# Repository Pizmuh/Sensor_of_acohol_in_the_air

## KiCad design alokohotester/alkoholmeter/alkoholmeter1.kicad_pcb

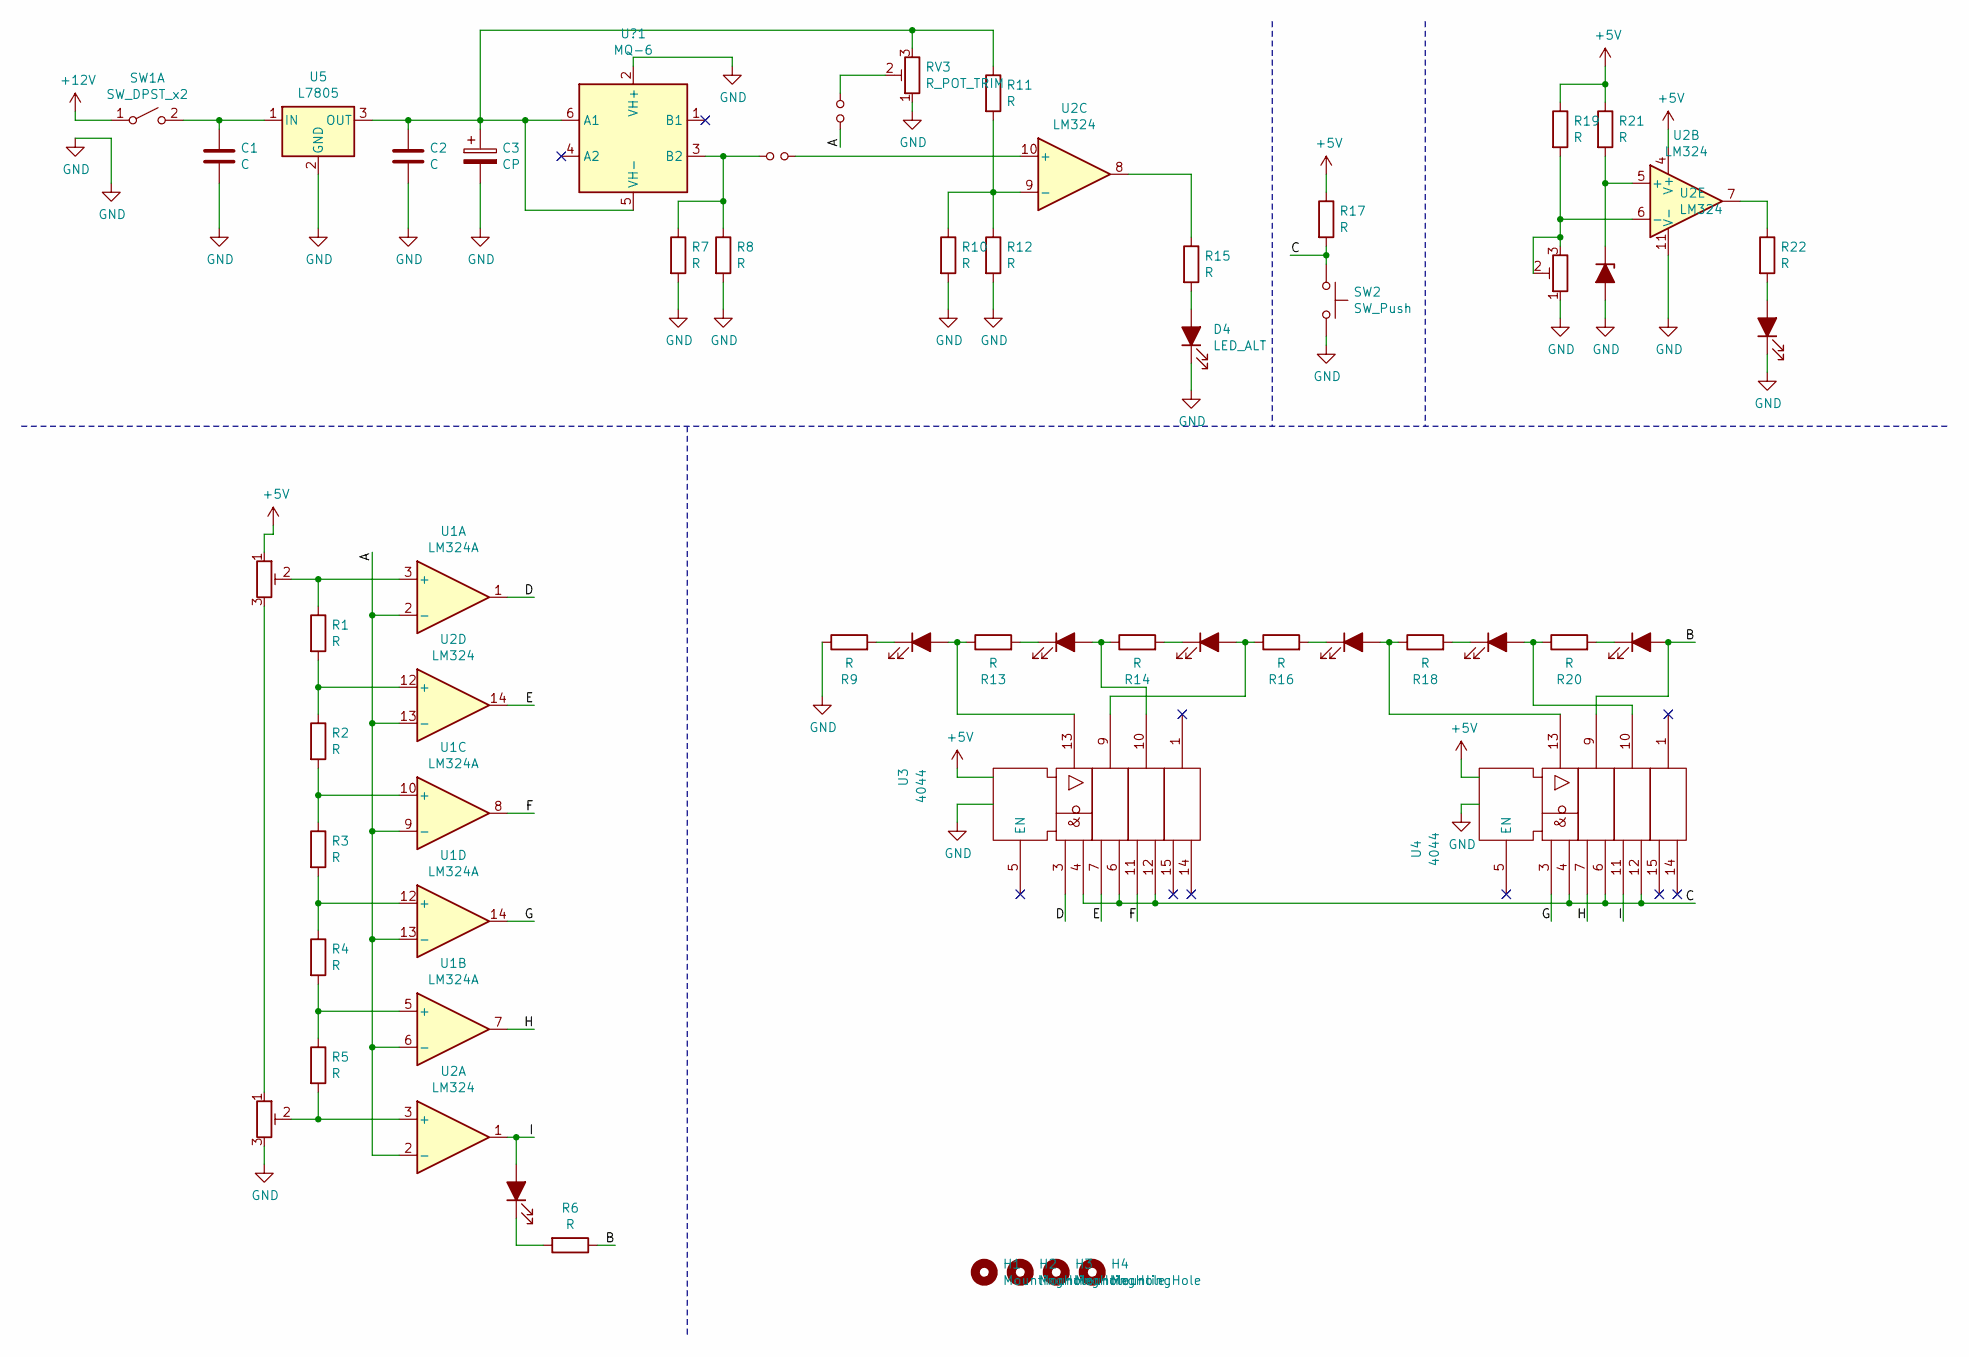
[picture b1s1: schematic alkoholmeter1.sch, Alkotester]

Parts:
C1, C2: C; CP_Radial_D5.0mm_P2.00mm
C3: CP; CP_Radial_D5.0mm_P2.00mm
D1, D2, D3, D4, D5, D6, D7, D9, D10: LED_ALT; LED_D5.0mm
D8: D_Zener_ALT; D_5KPW_P12.70mm_Horizontal
H1, H2, H3, H4: MountingHole; MountingHole_2.5mm
JP1, JP2: Jumper_NO_Small; SolderJumper-2_P1.3mm_Open_Pad1.0x1.5mm
R1, R2, R3, R4, R5, R6, R7, R8, R9, R10, R11, R12, R13, R14, R15, R16, R17, R18, R19, R20, R21, R22: R; R_Axial_DIN0207_L6.3mm_D2.5mm_P7.62mm_Horizontal
RV1, RV2, RV3, RV4: R_POT_TRIM; Potentiometer_ACP_CA6-H2,5_Horizontal
SW1: SW_DPST_x2; SW_E-Switch_EG1224_SPDT_Angled
SW2: SW_Push; SW_PUSH_6mm_H7.3mm
U1: LM324A; DIP825W47P254L1917H533Q14
U2: LM324; DIP825W47P254L1917H533Q14
U3, U4: 4044; DIL16
U5: L7805; TO254P470X1016X2019-3P
U?1: MQ-6

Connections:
+5V: R17.1, R19.1, R21.1, RV1.1, U2.4 (V+), U3.16 (Vdd), U4.16 (Vdd)
+12V: SW1.1 (A)
/A: JP2.1, U1.2 (-), U1.6 (-), U1.9 (-), U1.13 (-), U2.2 (-), U2.13 (-)
/B: D9.2 (A), R6.1, U4.9
/C: R17.2, SW2.1, U3.4, U3.6, U3.12, U4.4, U4.6, U4.12
/D: U1.1, U3.3
/E: U2.14, U3.7
/F: U1.8, U3.11
/G: U1.14, U4.3
/H: U1.7, U4.7
/I: D1.2 (A), U2.1, U4.11
GND: C1.2, C2.2, C3.2, D4.1 (K), D8.2 (A), D10.1 (K), R7.2, R8.2, R9.1, R10.2, R12.2, RV2.3, RV3.1, RV4.1, SW2.2, U2.11 (V-), U3.8 (Vss), U4.8 (Vss), U5.2 (GND), U?1.2 (VH+)
unnamed: C1.1, SW1.2 (B), U5.1 (IN)
unnamed: C2.1, C3.1, R11.1, RV3.3, U5.3 (OUT), U?1.5 (VH-), U?1.6 (A1)
unnamed: D1.1 (K), R6.2
unnamed: D2.1 (K), R9.2
unnamed: D2.2 (A), R13.1, U3.13
unnamed: D3.1 (K), R13.2
unnamed: D3.2 (A), R14.1, U3.10
unnamed: D4.2 (A), R15.2
unnamed: D5.1 (K), R14.2
unnamed: D5.2 (A), R16.1, U3.9
unnamed: D6.1 (K), R16.2
unnamed: D6.2 (A), R18.1, U4.13
unnamed: D7.1 (K), R18.2
unnamed: D7.2 (A), R20.1, U4.10
unnamed: D8.1 (K), R21.2, U2.5 (+)
unnamed: D9.1 (K), R20.2
unnamed: D10.2 (A), R22.2
unnamed: JP1.1, R7.1, R8.1, U?1.3 (B2)
unnamed: JP1.2, U2.10 (+)
unnamed: JP2.2, RV3.2
unnamed: R1.1, RV1.2, U1.3 (+)
unnamed: R1.2, R2.1, U2.12 (+)
unnamed: R2.2, R3.1, U1.10 (+)
unnamed: R3.2, R4.1, U1.12 (+)
unnamed: R4.2, R5.1, U1.5 (+)
unnamed: R5.2, RV2.2, U2.3 (+)
unnamed: R10.1, R11.2, R12.1, U2.9 (-)
unnamed: R15.1, U2.8
unnamed: R19.2, RV4.2, RV4.3, U2.6 (-)
unnamed: R22.1, U2.7
unnamed: RV1.3, RV2.1

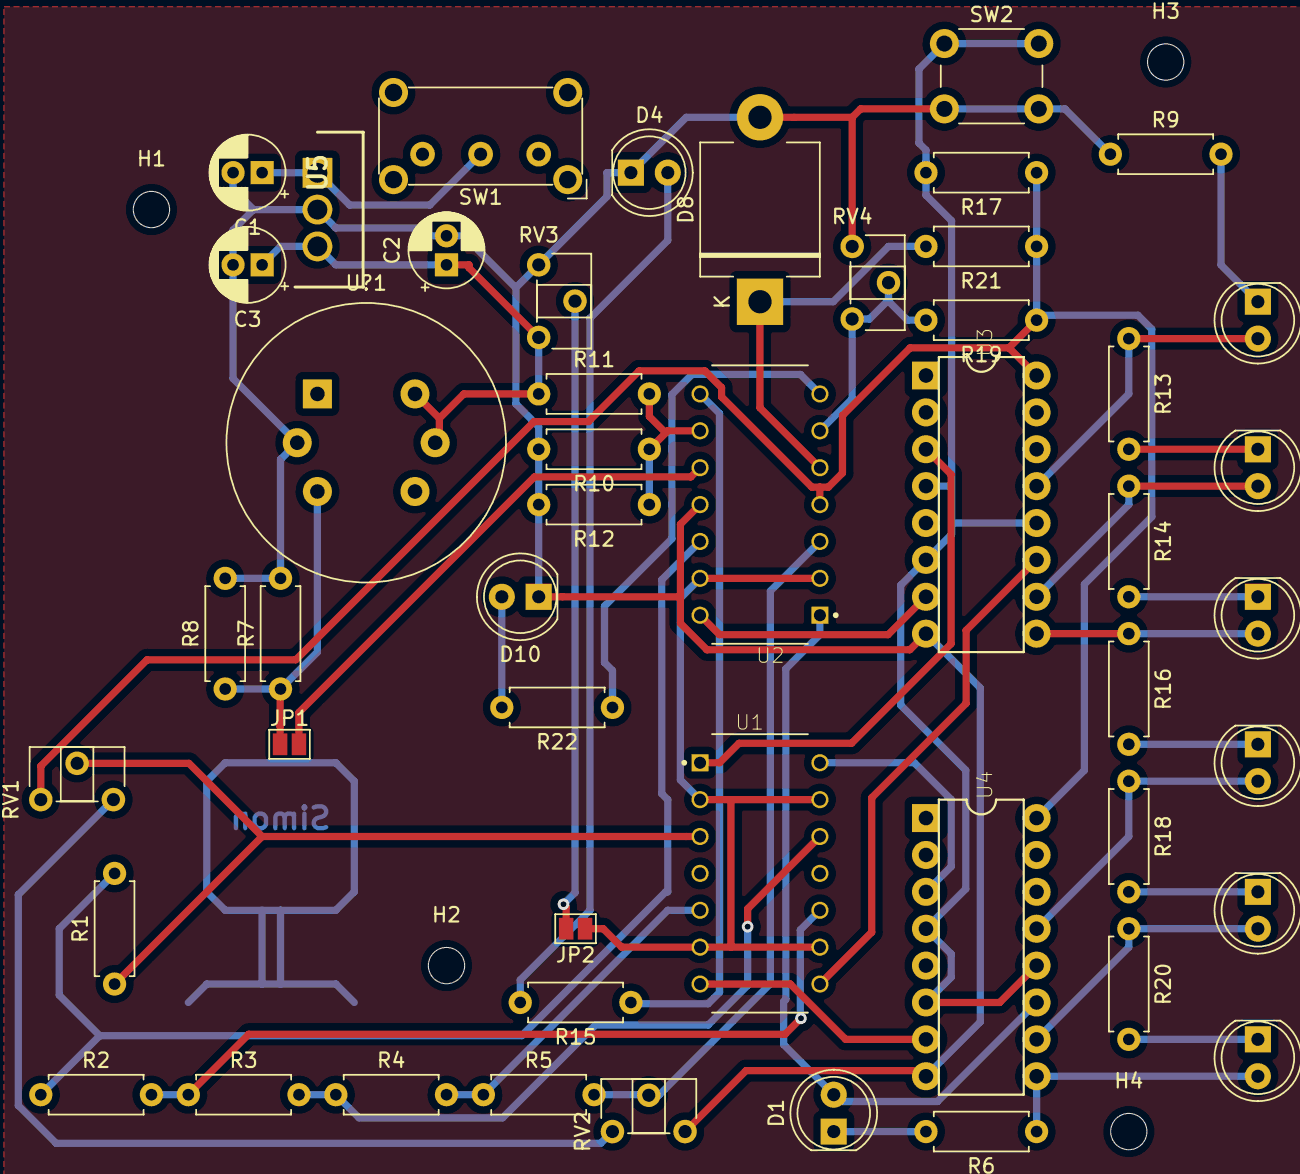
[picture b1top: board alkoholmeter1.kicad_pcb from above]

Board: 2 copper layers, 53 parts (0 on the bottom side), 42 nets.
